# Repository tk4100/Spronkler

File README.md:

# Spronkler
A sprinkler controller for raspberry pi, python controller software and KiCAD PCB design files.  Please please please don't edit
the "as-ordered" PCB files, for reasons that should be obvious.  They're useful for debugging boards of a particular revision.

# Software Architecture
Two main pieces, the webterface and the controller daemon.  The webUI is so far undesigned, but will communicate over ZMQ
to the controller daemon.

The controller daemon code is in Python, a master class with each major task in it's own thread/object, communicating with
inproc ZMQ. One of the aspects I wanted to explore was completely self-contained threads, each thread is responsible for
sanity in its own domain.  No matter what crazy commands are received via the ZMQ interface, a given thread should behave
safely.

## Controller
### Pin Daemon
Pretty simple here, controls actual GPIO outputs, and is responsible for preventing multiple channels from running at
once, as well as enforcing guard intervals etc.

### Schedule Daemon
Handles Schduling, with a total time-awareness of 365 days.  The plan is to have this daemon accept JSON objects
that represent a schedule, compare this new schedule with all other currently active schedules, reject the new
schedule if needed with a helpful message (ie, "conflicts with schedule 9, 'Rosemary dripline").  Similar logic
is required for activating/deactivating schedules.

Example schedule object.  It runs from May 1st, and repeats every 24 hours until October 1st.  The date is recorded in iso
format, but the year will be ignored. Looking at the schedule section, channel 1 runs for 5 minutes, channel 2 for 4 minutes,
and so on.
```json
{
   "name":"Demo Schedule",
   "start_time":"05-01T06:00:00",
   "end_time":"10-01T20:00:00",
   "interval_minutes":1440,
   "enabled":"true",
   "schedule":{
      "1":5,
      "2":4,
      "3":2,
      "4":4,
      "5":4,
      "6":5,
      "7":3,
      "9":5,
      "10":6,
      "12":6
   }
}
```

### API Daemon
The connection point to the webUI.  Probably will start out life as a simple bridge with one inproc ZMQ endpoint, and one
ipc or tcp endpoint.

# Hardware Architecture
A board powered by 24VAC which provides +5V on a standard Raspberry Pi header, as well as 3V3-safe inputs for a set of
opto-isolators.  ATM the power supply is linear, which doesn't work in practice, as it rapidly overheats from dropping
something like 29V.  The next rev will have a switching reg.

Pi Zero = ~125mA.  29 * 0.125 = **3.625W**

3.625W == Wayyy too much to dissipate in this package.  Anything over about 500mW requires a heatsink, and we don't want that.

## PSU
An LM317T and some caps.

***Note:*** There might be a noise problem here too.  I'm assuming the issue with Pi restarts is heat in the LM317, but
we might need some better noise suppression.  Don't forget to check before spinning a new board.

The [LMZ14201HTZ](https://www.digikey.com/product-detail/en/texas-instruments/LMZ14201HTZ-NOPB/LMZ14201HTZ-NOPBCT-ND/2533811) is
pricey, but appeals to my laziness.

# I/O
An opto-isolated SSR across common and each sprinkler channel.  Only a TVS diode is protecting the AC side of these, which
may not be right.  A FET with a pullup controls the inputs here, which are in series with LED indication on the board.

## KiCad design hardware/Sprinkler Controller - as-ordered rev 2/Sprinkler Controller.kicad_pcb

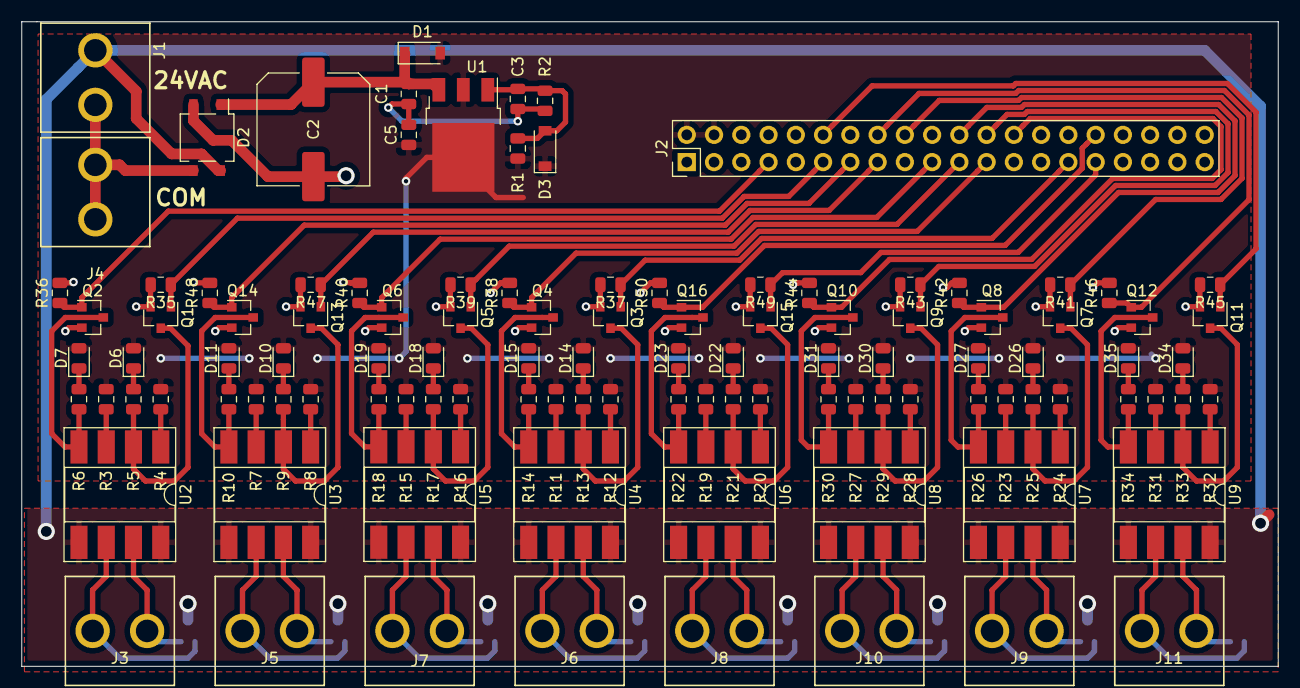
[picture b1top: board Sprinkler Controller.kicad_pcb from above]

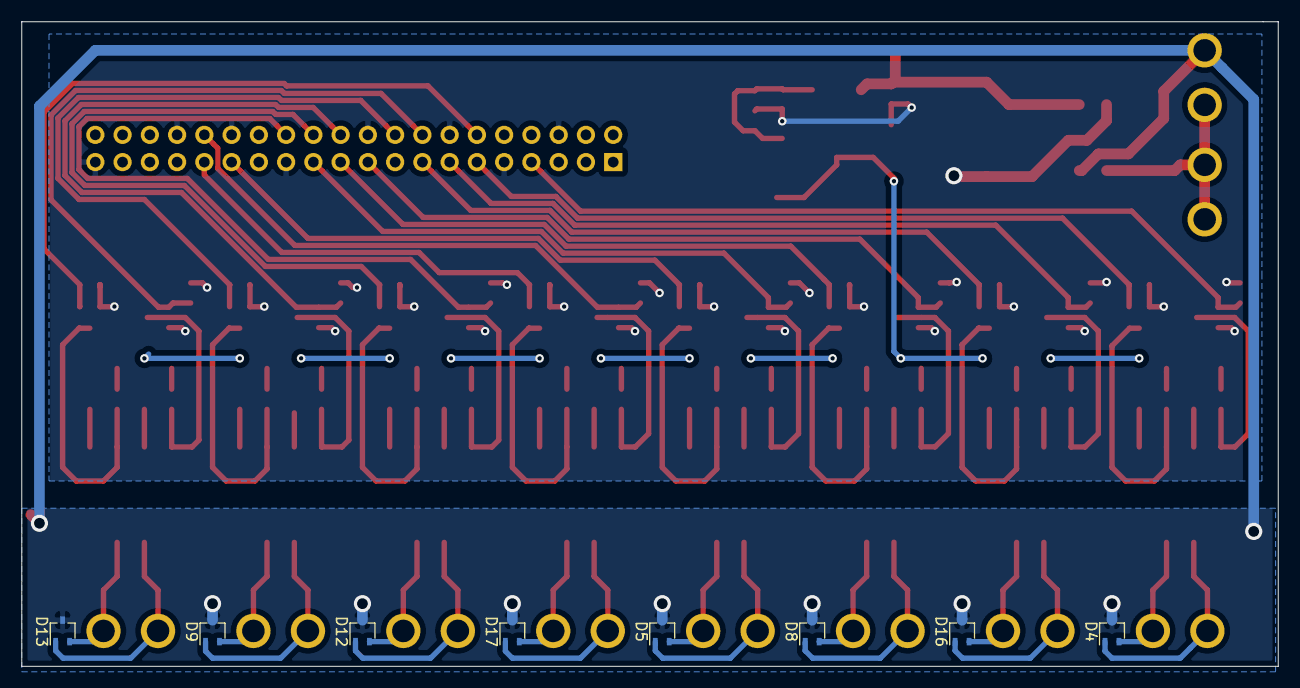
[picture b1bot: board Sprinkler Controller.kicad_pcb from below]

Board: 2 copper layers, 117.1 x 60.1 mm, 117 parts (8 on the bottom side), 86 nets.

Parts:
C1: 0.1u; C_0805_2012Metric
C2: 220u; C_Elec_10x10.2
C3, C5: 1u; C_0805_2012Metric
D1, D3: D_Small; D_SOD-123
D2: D_Bridge_+-AA; TO-269AA
D4, D5, D8, D9, D12, D13, D16, D17: PESD1CAN-U; SOT-323_SC-70
D6, D7, D10, D11, D14, D15, D18, D19, D22, D23, D26, D27, D30, D31, D34, D35: LED_Small; LED_0805_2012Metric
J1, J3, J4, J5, J6, J7, J8, J9, J10, J11: Conn_01x02; Terminal_2P_5mm
J2: Conn_02x20_Odd_Even; PinHeader_2x20_P2.54mm_Vertical
Q1, Q2, Q3, Q4, Q5, Q6, Q7, Q8, Q9, Q10, Q11, Q12, Q13, Q14, Q15, Q16: Q_NMOS_GSD; SOT-23
R1: 4K7; R_0805_2012Metric
R2: 14K; R_0805_2012Metric
R3, R4, R7, R8, R11, R12, R15, R16, R19, R20, R23, R24, R27, R28, R31, R32: 680R; R_0805_2012Metric
R5, R6, R9, R10, R13, R14, R17, R18, R21, R22, R25, R26, R29, R30, R33, R34: 2K; R_0805_2012Metric
R35, R36, R37, R38, R39, R40, R41, R42, R43, R44, R45, R46, R47, R48, R49, R50: 10K; R_0805_2012Metric
U1: LM317_3PinPackage; TO-252-3_TabPin2
U2, U3, U4, U5, U6, U7, U8, U9: G3VM-62F1; DIP-8_W8.89mm_SMDSocket_LongPads

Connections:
+5V: C5.1, D1.2, D3.1, D6.2, D7.2, D10.2, D11.2, D14.2, D15.2, D18.2, D19.2, D22.2, D23.2, D26.2, D27.2, D30.2, D31.2, D34.2, D35.2, J2.2, J2.4, R1.1, R3.2, R4.2, R7.2, R8.2, R11.2, R12.2, R15.2, R16.2, R19.2, R20.2, R23.2, R24.2, R27.2, R28.2, R31.2, R32.2, U1.2
+VDC: C1.1, C2.1, D1.1, D2.1, U1.3
/Channel_1: J2.11, Q1.1, R35.1
/Channel_2: J2.7, Q2.1, R36.1
/Channel_3: J2.15, Q13.1, R47.1
/Channel_4: J2.13, Q14.1, R48.1
/Channel_5: J2.21, Q5.1, R39.1
/Channel_6: J2.19, Q6.1, R40.1
/Channel_7: J2.29, Q3.1, R37.1
/Channel_8: J2.23, Q4.1, R38.1
/Channel_9: J2.16, Q12.1, R46.1
/Channel_10: J2.12, Q11.1, R45.1
/Channel_11: J2.26, Q10.1, R44.1
/Channel_12: J2.24, Q9.1, R43.1
/Channel_13: J2.32, Q16.1, R50.1
/Channel_15: J2.22, Q8.1, R42.1
/Channel_16: J2.18, Q7.1, R41.1
/sheet5ED885F3/C_1: J2.31, Q15.1, R49.1
GND: C1.2, C2.2, C3.2, C5.2, D2.2, J2.6, J2.9, J2.14, J2.20, J2.25, J2.30, J2.34, J2.39, Q1.2, Q2.2, Q3.2, Q4.2, Q5.2, Q6.2, Q7.2, Q8.2, Q9.2, Q10.2, Q11.2, Q12.2, Q13.2, Q14.2, Q15.2, Q16.2, R2.2, R35.2, R36.2, R37.2, R38.2, R39.2, R40.2, R41.2, R42.2, R43.2, R44.2, R45.2, R46.2, R47.2, R48.2, R49.2, R50.2
unnamed: C3.1, D3.2, R1.2, R2.1, U1.1
unnamed: D4.1, J3.2, U2.6
unnamed: D4.2, J3.1, U2.7
unnamed: D5.1, J6.2, U4.6
unnamed: D5.2, J6.1, U4.7
unnamed: D6.1, R5.1
unnamed: D7.1, R6.1
unnamed: D8.1, J7.2, U5.6
unnamed: D8.2, J7.1, U5.7
unnamed: D9.1, J9.2, U7.6
unnamed: D9.2, J9.1, U7.7
unnamed: D10.1, R9.1
unnamed: D11.1, R10.1
unnamed: D12.1, J10.2, U8.6
unnamed: D12.2, J10.1, U8.7
unnamed: D13.1, J11.2, U9.6
unnamed: D13.2, J11.1, U9.7
unnamed: D14.1, R13.1
unnamed: D15.1, R14.1
unnamed: D16.1, J5.2, U3.6
unnamed: D16.2, J5.1, U3.7
unnamed: D17.1, J8.2, U6.6
unnamed: D17.2, J8.1, U6.7
unnamed: D18.1, R17.1
unnamed: D19.1, R18.1
unnamed: D22.1, R21.1
unnamed: D23.1, R22.1
unnamed: D26.1, R25.1
unnamed: D27.1, R26.1
unnamed: D30.1, R29.1
unnamed: D31.1, R30.1
unnamed: D34.1, R33.1
unnamed: D35.1, R34.1
unnamed: Q1.3, R5.2, U2.2
unnamed: Q2.3, R6.2, U2.4
unnamed: Q3.3, R13.2, U4.2
unnamed: Q4.3, R14.2, U4.4
unnamed: Q5.3, R17.2, U5.2
unnamed: Q6.3, R18.2, U5.4
unnamed: Q7.3, R25.2, U7.2
unnamed: Q8.3, R26.2, U7.4
unnamed: Q9.3, R29.2, U8.2
unnamed: Q10.3, R30.2, U8.4
unnamed: Q11.3, R33.2, U9.2
unnamed: Q12.3, R34.2, U9.4
unnamed: Q13.3, R9.2, U3.2
unnamed: Q14.3, R10.2, U3.4
unnamed: Q15.3, R21.2, U6.2
unnamed: Q16.3, R22.2, U6.4
unnamed: R3.1, U2.3
unnamed: R4.1, U2.1
unnamed: R7.1, U3.3
unnamed: R8.1, U3.1
unnamed: R11.1, U4.3
unnamed: R12.1, U4.1
unnamed: R15.1, U5.3
unnamed: R16.1, U5.1
unnamed: R19.1, U6.3
unnamed: R20.1, U6.1
unnamed: R23.1, U7.3
unnamed: R24.1, U7.1
unnamed: R27.1, U8.3
unnamed: R28.1, U8.1
unnamed: R31.1, U9.3
unnamed: R32.1, U9.1
VAC+: D2.3, J1.1, J4.1, J4.2
VAC-: D2.4, D4.3, D5.3, D8.3, D9.3, D12.3, D13.3, D16.3, D17.3, J1.2, U2.5, U2.8, U3.5, U3.8, U4.5, U4.8, U5.5, U5.8, U6.5, U6.8, U7.5, U7.8, U8.5, U8.8, U9.5, U9.8

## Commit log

2020-08-21 copy to git
2020-08-23 reorg
2020-08-23 Readme updates
2020-08-23 changes to the schedule JSON
2020-08-23 no comment.
2020-08-23 Add in all the hardware stuff
2020-08-23 create scheduling conflict detector
2020-08-23 fix typos
2020-08-23 add addSchedule function
2020-08-23 remove some vetigial pinDaemon pieces
2020-08-23 i hate that i'm literally forced to comment each time
2020-08-23 if -> elif
2020-08-23 asdf
2020-08-23 import datetime
2020-08-23 update json
2020-08-23 forward def schedules
2020-08-23 add -> append
2020-08-23 go to the right depth
2020-08-23 debigging message
2020-08-23 tracking double schedule issue
2020-08-23 list messages
2020-08-23 add a paren
2020-08-23 add a print call i forgot
2020-08-23 float errors upstream
2020-08-23 another commit message for another simple typo
2020-08-23 move an assignment
2020-08-23 break placement
2020-08-23 typo
2020-08-23 message handling
2020-08-23 asdfa
2020-08-23 add second non-conflicting schedule
2020-08-23 a typo dammit
2020-08-23 add debugging verbosity
2020-08-23 a goddamn debugging statement because not everyone runs their code on their actual workstation for fuck's sake!!!
2020-08-23 or -> and
2020-08-23 one schedule can end and another start in the same minute.
2020-08-23 the Clarity in Debugging act of 1909
2020-08-23 constrain schedule projections in conflict detection to the end time of the schedule
2020-08-23 deal with schedules that begin and end within one repetition interval of each other
2020-08-23 start on timeout code for ScheduleDaemon loop
2020-08-23 timeout loop testing
2020-08-24 channel runner
2020-08-24 left off getting schedules to actually run. ATM we're not checking if a schedule should start based on interval, only based on per-year start time.
    We may need to convert the interval into a list of start and end times at import. That'd fuck up the conflict-checking code too.
2020-08-24 Add hardware info.
2020-08-24 add logging proper
2020-08-24 change log path, fix tabs, remove redundant thread naming in named logs.
2020-08-24 whoops log dirs
2020-08-24 Fix typo Add new constantly-running schedule Add check for schedules that self-interfere, ie they start more frequently than they can complete a cycle.
2020-08-24 debug log
2020-08-24 more verbose.
2020-08-24 datetime.datetime.now() makes it 2020, when we want the year to be the beginning of time.
2020-08-24 use proper methods
2020-08-24 Tricks to get "now" but without year information.
2020-08-24 .toisoformat() -> .isoformat()
2020-08-24 date format shenanigans
2020-08-24 ISO FORMAT MADNESSSSSSS
2020-08-24 fun times with logs
2020-08-24 condition logging
2020-08-24 sdgf
2020-08-24 so many comments for edited debugging statements.
2020-08-24 overconfidence in the stupidity of the past being gone now
2020-08-24 see what I mean?
2020-08-24 actually pass args to the schedule runner thread
2020-08-24 remove break
2020-08-24 yeah, gotta reference myself.
2020-08-24 try and actually remember the structure of your data
2020-08-24 inter-class communication
2020-08-24 don't invoke
2020-08-24 don't invoke, really
2020-08-24 logs
2020-08-24 ...whoopsie!
2020-08-24 ints and strings oh my!
2020-08-25 TIME FACTOR 1
2020-08-25 more verbose!
2020-08-25 debug the debugging
2020-08-25 programmers, man
2020-08-25 push entire schedule to runner thread
2020-08-25 log beautification
2020-08-25 Reset a schedule's running status after interval_minutes have passed since start. Doesn't reap old runner threads.
2020-08-25 TIME FACTOR 60
2020-08-25 schedule reactivation fixes
2020-08-25 better exception handling/reporting
2020-08-25 never use microseconds
2020-08-25 This version is broken, see the note on line 407
2020-08-25 yeah i can spell
2020-08-25 ...can't....stop....coding....
2020-08-26 some new schedules
2020-08-26 only start schedules near to their start hour/minute
2020-08-26 re-enable debug logging in conflict checker
2020-08-26 fix test schedule
2020-08-26 multi-schedule testing
2020-08-26 another
2020-08-26 8:35
2020-08-26 8:39
2020-08-26 8:40
2020-08-26 8:56
2020-08-26 8:59
2020-08-26 9:30, no debug
2020-08-26 debug again
2020-08-26 scheduler changes
2020-08-26 schelule
2020-08-26 lotsa prints
2020-08-26 log the next run time when schedules are added
2020-08-26 refs, man.
2020-08-26 Right, ref the one changed in the object, not the original that was passed in.
2020-08-26 can't just interval from right now.
2020-08-26 ok once more
2020-08-26 so many date to timestamp to date conversions
2020-08-26 yeah but this year tho
2020-08-26 udpate test sched
2020-08-26 test schedules
2020-08-26 eight
2020-08-26 ints
2020-08-26 damn syntax
2020-08-26 try timezones
2020-08-26 syntaxxxx
2020-08-26 datetime fun
2020-08-26 timezoooones
2020-08-27 go utc
2020-08-27 try using 2000 instead of 1900 to avoid platform time_t issues
2020-08-27 OMG WHY WAS DST EVER INVENTED I HATE EVERYTHING
